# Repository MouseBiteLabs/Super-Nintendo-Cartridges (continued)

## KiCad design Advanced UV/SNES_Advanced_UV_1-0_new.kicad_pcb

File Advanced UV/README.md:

# Super Nintendo Advanced UV Cartridge (SNES-8XJ8D-01C)

This is an updated design of my old <a href="https://mousebitelabs.com/2020/07/08/multi-function-snes-reproduction-board-guide/">SNES Advanced cartridge boards</a>, which utilize older UV EPROM chips 27C160 and/or 27C322. Functionally, this design is the same as the older one, but under the hood I have ported the project over from Eagle to KiCad, and heavily cleaned up the schematic and some of the trace routings. This version is also fully open source.

This cartridge covers over 95% of the entire SNES library, capable of any standard cartridge **but not those with co-processors, such as SA-1 or SuperFX.** You can backup games onto it with the following settings:
- All memory maps supported: LoROM, HiROM, ExLoROM, and ExHiROM
- Can be programmed to operate as a multicart, changing games by pressing the SNES reset button
- Up to 8 MB of ROM space for a single game or 4 MB of ROM space for two games
- Up to 128 KB of RAM space for a single game or two separate banks of 64 KB RAM space for two games

All gerbers and source files can be found in this repo, as again, this project is fully open source. Please read all instructions before attempting the project.

## Tutorial Video

This video is older, but still applies to this board.

## Important Things Before You Start

1) <a href="https://github.com/MouseBiteLabs/Super-Nintendo-Cartridges/wiki">Please review the wiki for more information about using the circuit boards, instructions for how to program them, and example builds.</a>
2) When soldering parts on, it's a good idea to put kapton tape or otherwise cover the bottom cartridge edge. You do not want to get solder on the cartridge contacts.
3) I am not responsible for any damage you do to your self or your property. Attempt this project at your own risk.
4) I do not guarantee design compatibility. You may encounter issues with certain games. There is also a chance I have made an error in the design or the BOM - if this is the case, I will do everything I can to address the problem as quickly as possible.
5) If you are using this board to make games other than for personal use, you must have permission from the originator to use and distribute any ROM images or other related material. You are responsible for making sure you adhere to any license requirements.

DO NOT use my circuit boards for profiting from stolen work - this especially includes homebrew content, ROM hacks, and using fan-made labels without permission from the originator. **Support ALL original creators!**

## Board Characteristics and Order Information

The zipped folder contains all the gerber files for this board. The following options **must** be chosen when ordering boards for yourself.

- Thickness: 1.2mm
- Surface Finish: ENIG
- Gold Fingers: Yes, 30° chamfer

You can use the zipped folder at any board fabricator you like. You may also buy the board from PCBWay using this link (disclosure: I receive 10% of the sale value to go towards future PCB orders of my own):

### Purchase from My Website

You can purchase this circuit board at my website, [https://mousebitelabs.store](https://mousebitelabs.store). Click the following image to be directed to the specific item listing:

### Purchase from Etsy

I also offer the board on Etsy, if you would rather purchase through there - click the banner to be redirected.

## Required Equipment

- You will need basic tools, like a soldering iron.
- You need a way to program the ROM chip(s). There are two ways I have programmed them in the past:
  - Using the <a href="https://xgecu.myshopify.com/products/xgecu-new-t48-tl866-3gprogrammer-v12-01-support-28000-ics-for-spi-nor-nand-flash-emmc-bga153-162-169-100-221-tsop-sop-plcc">T48 programmer</a> with my <a href="https://github.com/MouseBiteLabs/27C322-TL866-Adapter">27C322 to TL866 Programming Adatper</a> board. The programming adapter is compatible with the T48, and it allows you to program the 42-pin EPROMs (27C160 and 27C322) with the 40-pin T48 programmer.
  OR
  - Using the <a href="https://www.mcumall.com/store/index.php?route=product/product&path=66&product_id=85">GQ4x4 programmer</a> with the ZIF adapter board that comes with it.
- This cartridge uses the PIC12F629 with the <a href="https://sd2snes.de/blog/cool-stuff/supercic">SuperCIC code</a> to fake out the lockout chip. You will need a way to program these PIC chips. I use the T48 to do so, but you can also use something like the <a href="https://www.microchip.com/en-us/development-tool/pg164130">PICkit 3.</a> Note that if you have region modded your SNES, you won't need the lockout chips in the cartridges.

## How to Program

<a href="https://github.com/MouseBiteLabs/Super-Nintendo-Cartridges/wiki/Preparing-the-ROM">Please check out the wiki pages on how to prepare the ROM and program the cartridge.</a>

## Board Configurations

This board is highly customizable. You *do not* need every single part on this board to make a game. The game you want to make is mainly dependent on the memory mapping (LoROM, HiROM, etc), the ROM size, and the RAM size. Depending on your needs, you only need to solder on certain components, which you can find below in the BOM section. You will also need to configure the game with the various solder jumpers on the back of the board.

<a href="https://github.com/MouseBiteLabs/Super-Nintendo-Cartridges/wiki/Advanced-UV">**I highly recommend checking out the various examples of board configurations on the wiki.**</a>

### Components Required

I've split up the requisite parts into a few different "Groups" which you can find a comprehensive list for in the BOM section a few sections down from this one.

- **Every board needs Group A components.** You can make LoRom or HiROM games that have no RAM and are up to 4 MB large with this configuration.
- If you need RAM space, **add Group B components.** This will add up to 128 KB of RAM space.
- If your game is larger than 4 MB, it will use the ExLoROM or ExHiROM memory mapping. **Add Group C components for this.**
- For multicarts, you can make a board with two games on it up to 4 MB each. You will need Group C components, **as well as Group D components.**

#### Socket Configurations

If your game is the LoROM or ExLoROM mapping type, solder U3 (and U4 if necessary) in the bottom set of sockets (labeled "LO" on the left side). If your game is of the HiROM or ExHiROM mapping type, solder U3 (and U4 if necessary) in the top set of sockets (labeled "HI" on the left side). Furthermore, if you are making a LoROM or ExLoROM game that has SRAM, then populate the U8L socket. If you are making a HiROM or ExHiROM game that has SRAM, then populate the U8H socket. Note that you can populate both U8L and U8H without issue, if you want.

If you are making a multicart, both games must be of the *same* mapping type. You cannot make one HiROM and one LoROM game in a multicart.

Keep in mind that the 27C160 can hold up to 2 MB of ROM data, and the 27C322 can hold up to 4 MB. You can use either of those chips in ROM slots 1 and 2, but if you are going to make an ExLoROM or ExHiROM game, ROM1 needs to be a 27C322. ROM2 in this case *can* be a 27C160, but only if the ROM is 6 MB total in size.

### Solder Jumpers

There are two types of solder jumper pads on the board - the 2-segment and 3-segment. For the 2-segment pads, if they need to be connected, simply bridge the two with solder. For the 3-segment pads, use a solder bridge on the middle pad to either side depending on the option you need.

#### U8 Bypass

This is the only set of pads on the front of the board. If your game does not use SRAM, then you must solder these pads together. **Do not solder these pads if your game uses SRAM.**

#### U3/U4 Configuration

On the reverse side of U3 and U4 are three sets of pads used to set what kind of EPROM you are using, and in the case of the 27C322, what mapping type you are using.

Keep in mind that if you are using both ROM1 and ROM2, both EPROMs *must* be in the same mapping type sockets - either both LoROM or both HiROM. You cannot mix the two mapping types between EPROMs. You can however use one 27C322 in ROM1 and a 27C160 in ROM2 for EX-mode games, or 27C160 in ROM1 as well if making a multicart.

#### LoROM/HiROM

These are all 3-segment pads. They only need to be configured on the back if you are making a game that contains SRAM.

#### Single/Multi

The pads on the bottom right of the back of the board are mandatory for every game. Solder the middle pad to the top for single game configuration, or to the bottom for multicart configuration. The pads on the top middle of the back of the board only need to be configured if your cartridge uses SRAM.

#### SRAM Size

The set of pads at the top left underneath the SRAM chip configure the size of the SRAM that the SNES will see. All pads must be configured if you are using SRAM, and each set of 2 should be soldered in the same direction. The example picture below shows a game configured for 256 Kbit of SRAM. **It is important to note these numbers represent the SRAM in BITS, not BYTES. To figure out the BYTES of SRAM, take the numbers here and divide by 8.**

Note: If you want to set the RAM size to zero, but still have a RAM chip installed, then simply unsolder the right-most HIROM/LOROM solder pads on the backside of the board.

### Multicart Configuration

If you are setting you cartridge up for a multicart, you must bend out pin 2 (AS6C1008) or pin 1 (AS6C62256) on the SRAM chip and solder it to the outside hole.

## Estimating Battery Life

To accurately estimate the battery life, measure the voltage across R1 using a multimeter in DC mV mode, touching the probes to the two test point pads on either side of R1. You should read something around 1 mV or less. If you are severely higher than 10 mV, like in the 100's of mV, then you have a problem on your board.

Once you have a suitable voltage, find the milliamp-hour rating of your selected battery (preferrably from a datasheet). For example, a Renata CR2032 battery is rated for 225 mAh.

Now to estimate battery life, take the voltage measurement in mV and the battery rating in mAh, and plug it into this equation: 

Time (years) = Resistance of R1 (ohms) * Battery capacity (mAh) / Voltage (mV) / 8760

The factor of 8760 is for converting years to hours (24 hours in a day, 365 days in a year). The resistance of R1 is 1000 ohms. So for an example, if you measured 1 mV on R1 and are using a Renata CR2032, you would get 1000 * 225 / 1 / 8760 = **25.7 years.**

## Troubleshooting

<a href="https://github.com/MouseBiteLabs/Super-Nintendo-Cartridges/wiki/Troubleshooting-Tips">Please check out the wiki pages for troubleshooting tips.</a>

## Bill of Materials (BOM)

The component groups required for the build you want to make are detailed above.

### Mouser Shopping Cart

The following cart has *the maximum amount* of parts you would potentially need on a single board (essentially, a multicart), plus a few extras of the passive components due to price breaks. Importantly, though, this does not include the UV EPROM chips (27C160 and 27C322) because those are only available as old stock from places like AliExpress and/or eBay.

https://www.mouser.com/ProjectManager/ProjectDetail.aspx?AccessID=686eaad9eb

### Group A - 4 MB ROM, No RAM

| Reference | Value/Part Number | Package              | Description                     | Source                                           |
| --------- | ----------------- | -------------------- | ------------------------------- | ------------------------------------------------ |
| C1        | 22u               | Radial 2.5mm spacing | Aluminum Electrolytic Capacitor | [https://mou.sr/4lzfiK1](https://mou.sr/4lzfiK1) |
| C2        | 0.1u              | Radial 2.5mm spacing | Ceramic Capacitor               | [https://mou.sr/481ILov](https://mou.sr/481ILov) |
| C3        | 0.1u              | Radial 2.5mm spacing | Ceramic Capacitor               | [https://mou.sr/481ILov](https://mou.sr/481ILov) |
| C6        | 0.1u              | Radial 2.5mm spacing | Ceramic Capacitor               | [https://mou.sr/481ILov](https://mou.sr/481ILov) |
| C7        | 0.1u              | Radial 2.5mm spacing | Ceramic Capacitor               | [https://mou.sr/481ILov](https://mou.sr/481ILov) |
| C9        | 0.1u              | Radial 2.5mm spacing | Ceramic Capacitor               | [https://mou.sr/481ILov](https://mou.sr/481ILov) |
| U2A       | PIC12F629         | DIP-8                | PIC Microcontroller             | [https://mou.sr/3XuEZzO](https://mou.sr/3XuEZzO) |
| U2B       | PIC12F629         | SOIC-8               | PIC Microcontroller             | [https://mou.sr/4dSUh90](https://mou.sr/4dSUh90) |
| U3        | 27C322, 27C160    | DIP-42               | UV EPROM                        | AliExpress, eBay                                 |
| U6        | 74HCT257          | DIP-16               | Multiplexer                     | [https://mou.sr/3EvChVI](https://mou.sr/3EvChVI) |
| U7        | 74HCT257          | DIP-16               | Multiplexer                     | [https://mou.sr/3EvChVI](https://mou.sr/3EvChVI) |
| U9        | 74HCT139          | DIP-16               | Decoder                         | [https://mou.sr/441VXuJ](https://mou.sr/441VXuJ) |

### Group B - adds 32 KB of RAM

| Reference | Value/Part Number | Package              | Description                     | Source                                           |
| --------- | ----------------- | -------------------- | ------------------------------- | ------------------------------------------------ |
| B1        | CR2032            | CR2032               | Coin Cell Battery               | [https://mou.sr/3Wj2m0G](https://mou.sr/3Wj2m0G) |
| CB        | 22u               | Radial 2.5mm spacing | Aluminum Electrolytic Capacitor | [https://mou.sr/4lzfiK1](https://mou.sr/4lzfiK1) |
| C5        | 0.1u              | Radial 2.5mm spacing | Ceramic Capacitor               | [https://mou.sr/481ILov](https://mou.sr/481ILov) |
| C8        | 0.1u              | Radial 2.5mm spacing | Ceramic Capacitor               | [https://mou.sr/481ILov](https://mou.sr/481ILov) |
| D1        | BAT85             | DO-35-2              | Schottky Diode                  | [https://mou.sr/49GVT4m](https://mou.sr/49GVT4m) |
| D2        | BAT85             | DO-35-2              | Schottky Diode                  | [https://mou.sr/49GVT4m](https://mou.sr/49GVT4m) |
| D3        | BAT85             | DO-35-2              | Schottky Diode                  | [https://mou.sr/49GVT4m](https://mou.sr/49GVT4m) |
| Q1        | 2N3904            | TO-92-3 / SOT-23-3   | NPN BJT                         | THT: [https://mou.sr/3HlkU91](https://mou.sr/3HlkU91), SMT: [https://mou.sr/3C8piaZ](https://mou.sr/3C8piaZ) |
| R1        | 1k                | Axial                | Resistor                        | [https://mou.sr/4hYkrZr](https://mou.sr/4hYkrZr) |
| R2        | 100k              | Axial                | Resistor                        | [https://mou.sr/3Ib4SgO](https://mou.sr/3Ib4SgO) |
| R3        | 10k               | Axial                | Resistor                        | [https://mou.sr/42AN0WU](https://mou.sr/42AN0WU) |
| R4        | 1k                | Axial                | Resistor                        | [https://mou.sr/4hYkrZr](https://mou.sr/4hYkrZr) |
| R5        | 10k               | Axial                | Resistor                        | [https://mou.sr/42AN0WU](https://mou.sr/42AN0WU) |
| U5        | AS6C62256         | DIP-28               | SRAM                            | [https://mou.sr/3HlZ0mh](https://mou.sr/3HlZ0mh) |
| U8        | 74HCT139          | DIP-16               | Decoder                         | [https://mou.sr/441VXuJ](https://mou.sr/441VXuJ) |

### Group B (Optional) - adds 128 KB of RAM (instead of 32 KB)

Replace U5 in Group B above with the part detailed here, and add the other three components. **I personally recommend sticking to the AS6C62256 SRAM chip unless you absolutely need more RAM space.**

| Reference | Value/Part Number | Package | Description | Source                                           |
| --------- | ----------------- | ------- | ----------- | ------------------------------------------------ |
| Q2        | 2N3904            | TO-92-3 | NPN BJT     | [https://mou.sr/3HlkU91](https://mou.sr/3HlkU91) |
| R6        | 100k              | Axial   | Resistor    | [https://mou.sr/3Ib4SgO](https://mou.sr/3Ib4SgO) |
| R7        | 10k               | Axial   | Resistor    | [https://mou.sr/42AN0WU](https://mou.sr/42AN0WU) |
| U5        | AS6C1008          | DIP-32  | SRAM        | [https://mou.sr/3hNkGxg](https://mou.sr/3hNkGxg) |

### Group C - Adds 4 MB ROM for ExLoROM/ExHiROM or multicarts

| Reference | Value/Part Number | Package              | Description       | Source                                           |
| --------- | ----------------- | -------------------- | ----------------- | ------------------------------------------------ |
| C4        | 0.1u              | Radial 2.5mm spacing | Ceramic Capacitor | [https://mou.sr/481ILov](https://mou.sr/481ILov) |
| U4        | 27C322, 27C160    | DIP-42               | UV EPROM          | AliExpress, eBay                                 |

### Group D - Enables multicart mode

| Reference | Value/Part Number | Package              | Description       | Source                                           |
| --------- | ----------------- | -------------------- | ----------------- | ------------------------------------------------ |
| C10       | 0.1u              | Radial 2.5mm spacing | Ceramic Capacitor | [https://mou.sr/481ILov](https://mou.sr/481ILov) |
| U10       | 74HCT74           | DIP-14               | Flip-flop         | [https://mou.sr/3YEiVo8](https://mou.sr/3YEiVo8) |

## Revision History

### v1.0 - Re-release

- Release of the KiCad-ported version of my original SNES Advanced cart design
- Removed the "SRAM Enable" pads and made the SRAM always enabled
- HOTFIX: changed QR code, added open source hardware logo

## Acknowledgements

- Continual thanks to all in the nesdev community for their resources, design tips, and support throughout the past half-decade. This design was one of my original ones that was improved through their help and feedback when I was first starting out.

## License

<br />This work is licensed under a <a rel="license" href="http://creativecommons.org/licenses/by-sa/4.0/">Creative Commons Attribution-ShareAlike 4.0 International License</a>. You are able to copy and redistribute the material in any medium or format, as well as remix, transform, or build upon the material for any purpose (even commercial) - but you **must** give appropriate credit, provide a link to the license, and indicate if any changes were made.

©MouseBiteLabs 2025

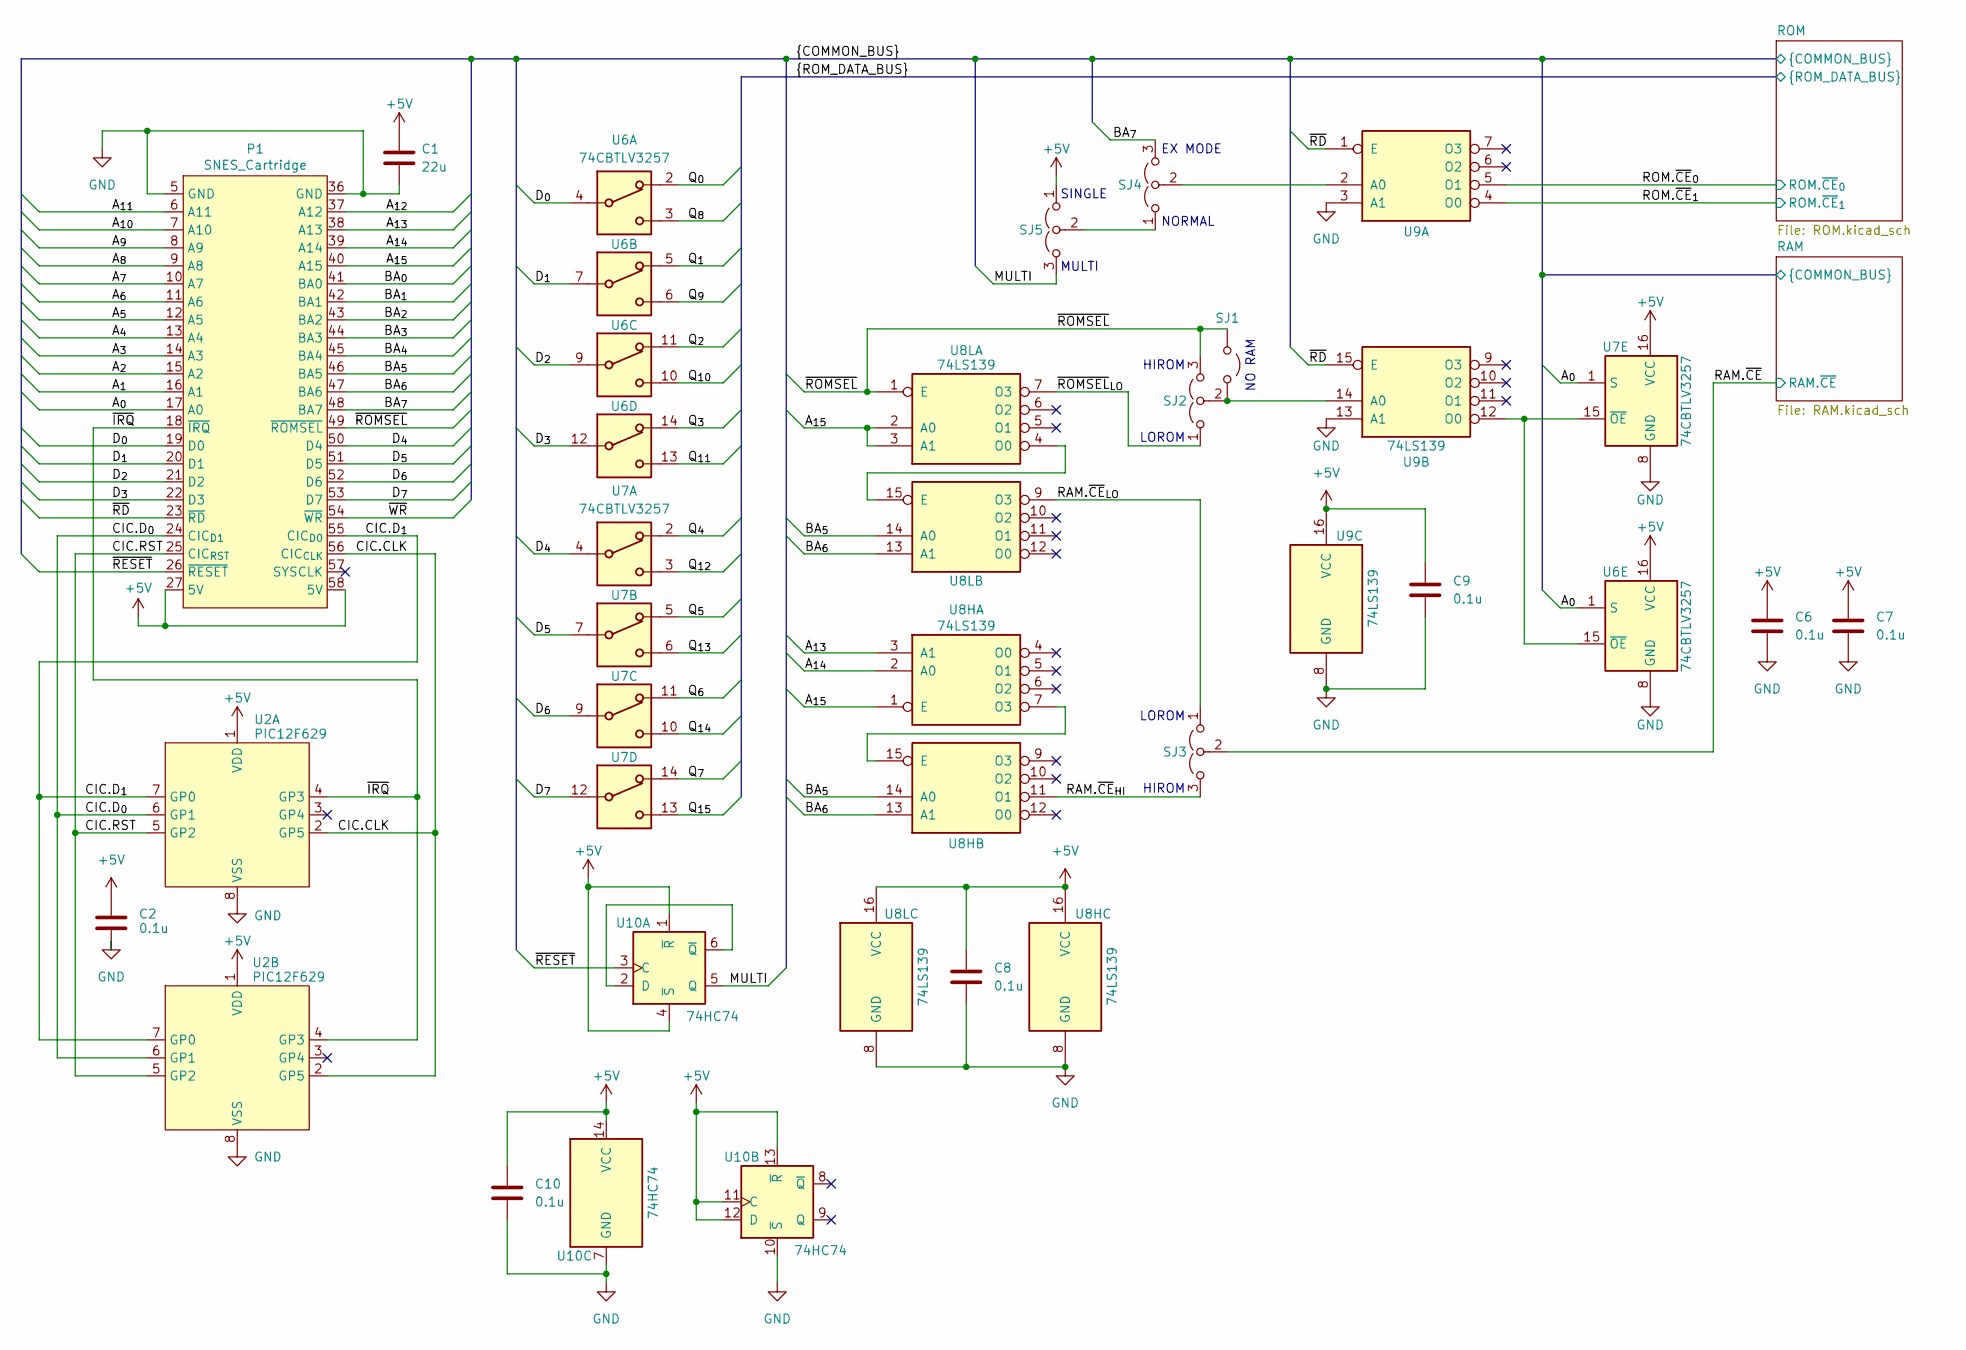
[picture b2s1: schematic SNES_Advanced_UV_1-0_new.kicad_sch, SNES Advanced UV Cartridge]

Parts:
C1: 22u; CP_Radial_D5.0mm_P2.50mm
C2, C6, C7, C8, C9, C10: 0.1u; C_THT
P1: SNES_Cartridge; Cart_Edge_SNES_Standard
SJ1: Jumper_2_Open; SJ
SJ2, SJ3, SJ4, SJ5: Jumper_3_Open; SJ_2
U2A: PIC12F629; SOIC-8_3.9x4.9mm_P1.27mm
U2B: PIC12F629; DIP-8_W7.62mm
U6, U7: 74CBTLV3257; DIP-16_W7.62mm
U8H, U8L, U9: 74LS139; DIP-16_W7.62mm
U10: 74HC74; DIP-14_W7.62mm

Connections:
+5V: C1.1, C2.1, C6.1, C7.1, C8.1, C9.1, C10.1, P1.27 (5V), P1.58 (5V), SJ5.1 (A), U2A.1 (VDD), U2B.1 (VDD), U6.16 (VCC), U7.16 (VCC), U8H.16 (VCC), U8L.16 (VCC), U9.16 (VCC), U10.1 (~R), U10.4 (~S), U10.11 (C), U10.12 (D), U10.13 (~R), U10.14 (VCC); also elsewhere on the board
/A_{0}: P1.17 (A0), U6.1 (S), U7.1 (S); also elsewhere on the board
/A_{1}: P1.16 (A1); also elsewhere on the board
/A_{2}: P1.15 (A2); also elsewhere on the board
/A_{3}: P1.14 (A3); also elsewhere on the board
/A_{4}: P1.13 (A4); also elsewhere on the board
/A_{5}: P1.12 (A5); also elsewhere on the board
/A_{6}: P1.11 (A6); also elsewhere on the board
/A_{7}: P1.10 (A7); also elsewhere on the board
/A_{8}: P1.9 (A8); also elsewhere on the board
/A_{9}: P1.8 (A9); also elsewhere on the board
/A_{10}: P1.7 (A10); also elsewhere on the board
/A_{11}: P1.6 (A11); also elsewhere on the board
/A_{12}: P1.37 (A12); also elsewhere on the board
/A_{13}: P1.38 (A13), U8H.3 (A1); also elsewhere on the board
/A_{14}: P1.39 (A14), U8H.2 (A0); also elsewhere on the board
/A_{15}: P1.40 (A15), U8H.1 (E), U8L.2 (A0), U8L.3 (A1); also elsewhere on the board
/BA_{0}: P1.41 (BA0); also elsewhere on the board
/BA_{1}: P1.42 (BA1); also elsewhere on the board
/BA_{2}: P1.43 (BA2); also elsewhere on the board
/BA_{3}: P1.44 (BA3); also elsewhere on the board
/BA_{4}: P1.45 (BA4); also elsewhere on the board
/BA_{5}: P1.46 (BA5), U8H.14 (A0), U8L.14 (A0); also elsewhere on the board
/BA_{6}: P1.47 (BA6), U8H.13 (A1), U8L.13 (A1); also elsewhere on the board
/BA_{7}: P1.48 (BA7), SJ4.3 (B)
/CIC.CLK: P1.56 (CIC_{CLK}), U2A.2 (GP5), U2B.2 (GP5)
/CIC.D_{0}: P1.55 (CIC_{D0}), U2A.7 (GP0), U2B.7 (GP0)
/CIC.D_{1}: P1.24 (CIC_{D1}), U2A.6 (GP1), U2B.6 (GP1)
/CIC.RST: P1.25 (CIC_{RST}), U2A.5 (GP2), U2B.5 (GP2)
/D_{0}: P1.19 (D0), U6.4; also elsewhere on the board
/D_{1}: P1.20 (D1), U6.7; also elsewhere on the board
/D_{2}: P1.21 (D2), U6.9; also elsewhere on the board
/D_{3}: P1.22 (D3), U6.12; also elsewhere on the board
/D_{4}: P1.50 (D4), U7.4; also elsewhere on the board
/D_{5}: P1.51 (D5), U7.7; also elsewhere on the board
/D_{6}: P1.52 (D6), U7.9; also elsewhere on the board
/D_{7}: P1.53 (D7), U7.12; also elsewhere on the board
/MULTI: SJ5.3 (B), U10.5 (Q); also elsewhere on the board
/Q_{0}: U6.2; also elsewhere on the board
/Q_{1}: U6.5; also elsewhere on the board
/Q_{2}: U6.11; also elsewhere on the board
/Q_{3}: U6.14; also elsewhere on the board
/Q_{4}: U7.2; also elsewhere on the board
/Q_{5}: U7.5; also elsewhere on the board
/Q_{6}: U7.11; also elsewhere on the board
/Q_{7}: U7.14; also elsewhere on the board
/Q_{8}: U6.3; also elsewhere on the board
/Q_{9}: U6.6; also elsewhere on the board
/Q_{10}: U6.10; also elsewhere on the board
/Q_{11}: U6.13; also elsewhere on the board
/Q_{12}: U7.3; also elsewhere on the board
/Q_{13}: U7.6; also elsewhere on the board
/Q_{14}: U7.10; also elsewhere on the board
/Q_{15}: U7.13; also elsewhere on the board
/RAM.~CE: SJ3.2 (C); also elsewhere on the board
/RAM.~CE_{HI}: SJ3.3 (B), U8H.11 (O1)
/RAM.~CE_{LO}: SJ3.1 (A), U8L.9 (O3)
/ROM.~CE_{0}: U9.5 (O1); also elsewhere on the board
/ROM.~CE_{1}: U9.4 (O0); also elsewhere on the board
/~IRQ: P1.18 (~IRQ), U2A.4 (GP3), U2B.4 (GP3)
/~RD: P1.23 (~RD), U9.1 (E), U9.15 (E); also elsewhere on the board
/~RESET: P1.26 (~RESET), U10.3 (C); also elsewhere on the board
/~ROMSEL: P1.49 (~ROMSEL), SJ1.2 (B), SJ2.3 (B), U8L.1 (E)
/~ROMSEL_{LO}: SJ2.1 (A), U8L.7 (O3)
/~WR: P1.54 (~WR); also elsewhere on the board
GND: C1.2, C2.2, C6.2, C7.2, C8.2, C9.2, C10.2, P1.5 (GND), P1.36 (GND), U2A.8 (VSS), U2B.8 (VSS), U6.8 (GND), U7.8 (GND), U8H.8 (GND), U8L.8 (GND), U9.3 (A1), U9.8 (GND), U9.13 (A1), U10.7 (GND), U10.10 (~S); also elsewhere on the board
unnamed: SJ1.1 (A), SJ2.2 (C), U9.14 (A0)
unnamed: SJ4.1 (A), SJ5.2 (C)
unnamed: SJ4.2 (C), U9.2 (A0)
unnamed: U6.15 (~OE), U7.15 (~OE), U9.12 (O0)
unnamed: U8H.7 (O3), U8H.15 (E)
unnamed: U8L.4 (O0), U8L.15 (E)
unnamed: U10.2 (D), U10.6 (~Q)

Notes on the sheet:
SINGLE MULTI
HIROM LOROM
NO RAM
EX MODE NORMAL
LOROM HIROM

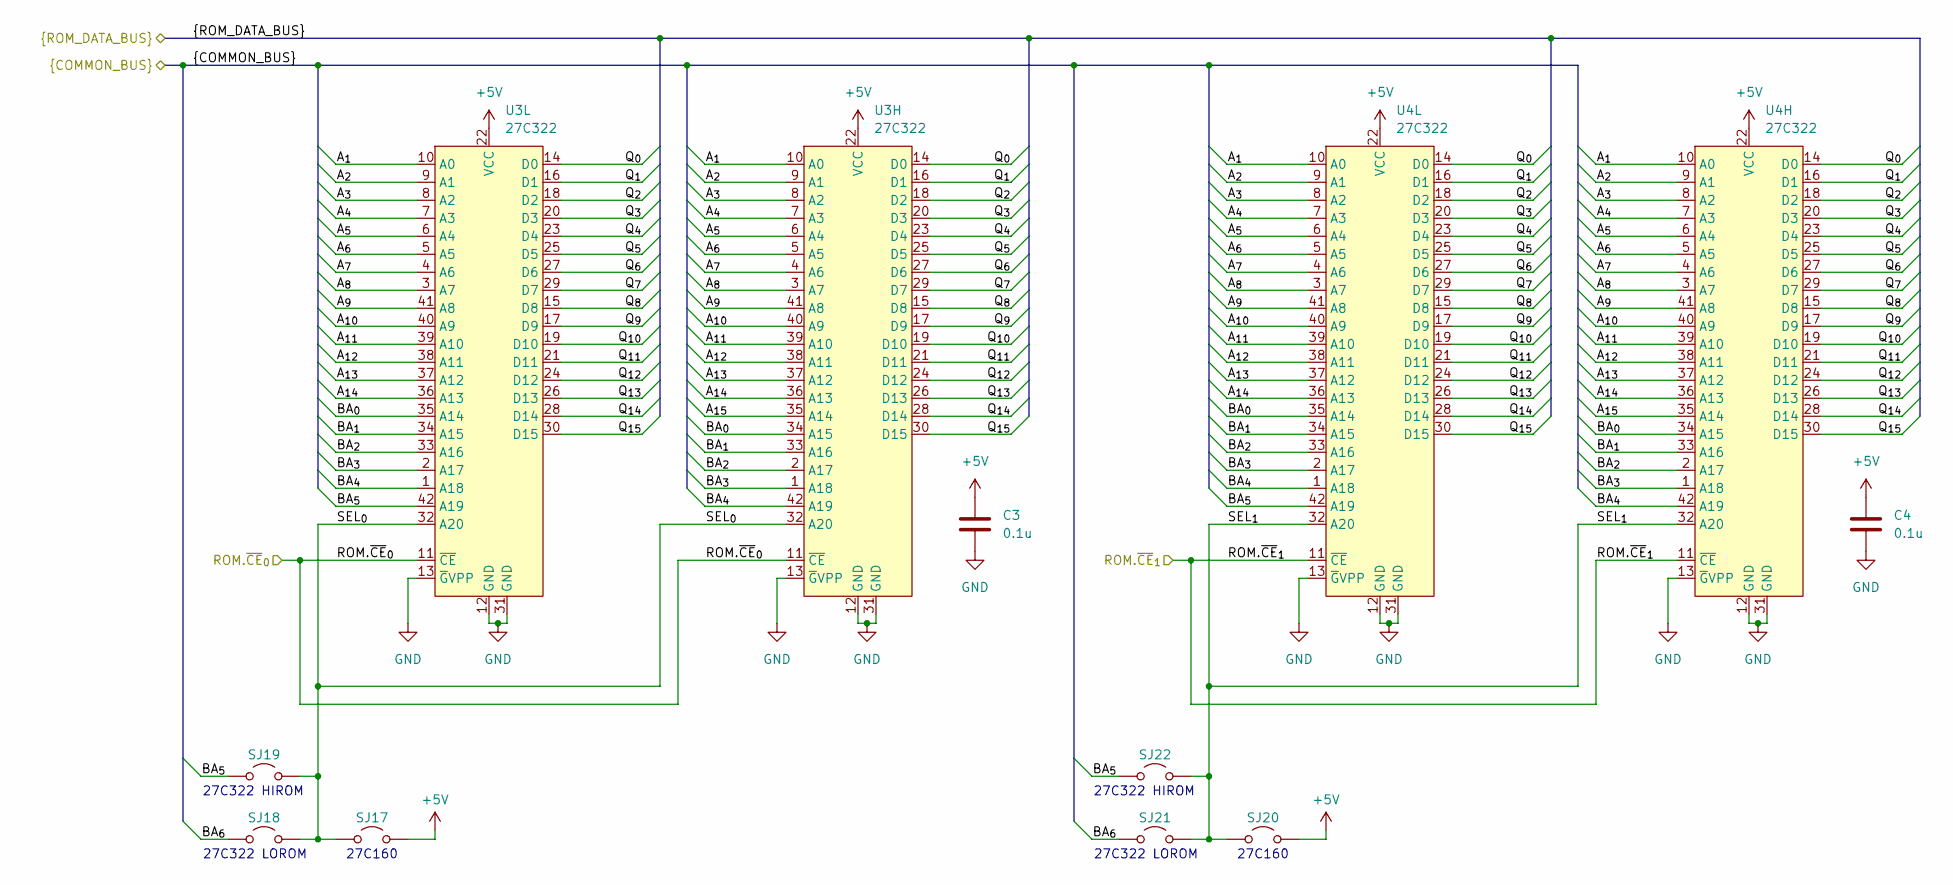
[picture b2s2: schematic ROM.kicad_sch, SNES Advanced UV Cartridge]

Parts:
C3, C4: 0.1u; C_THT
SJ17, SJ18, SJ19, SJ20, SJ21, SJ22: Jumper_2_Open; SJ
U3H, U3L, U4H, U4L: 27C322; DIP-42_W15.24mm

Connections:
+5V: C3.1, C4.1, SJ17.1 (A), SJ20.1 (A), U3H.22 (VCC), U3L.22 (VCC), U4H.22 (VCC), U4L.22 (VCC); also elsewhere on the board
/A_{1}: U3H.10 (A0), U3L.10 (A0), U4H.10 (A0), U4L.10 (A0); also elsewhere on the board
/A_{2}: U3H.9 (A1), U3L.9 (A1), U4H.9 (A1), U4L.9 (A1); also elsewhere on the board
/A_{3}: U3H.8 (A2), U3L.8 (A2), U4H.8 (A2), U4L.8 (A2); also elsewhere on the board
/A_{4}: U3H.7 (A3), U3L.7 (A3), U4H.7 (A3), U4L.7 (A3); also elsewhere on the board
/A_{5}: U3H.6 (A4), U3L.6 (A4), U4H.6 (A4), U4L.6 (A4); also elsewhere on the board
/A_{6}: U3H.5 (A5), U3L.5 (A5), U4H.5 (A5), U4L.5 (A5); also elsewhere on the board
/A_{7}: U3H.4 (A6), U3L.4 (A6), U4H.4 (A6), U4L.4 (A6); also elsewhere on the board
/A_{8}: U3H.3 (A7), U3L.3 (A7), U4H.3 (A7), U4L.3 (A7); also elsewhere on the board
/A_{9}: U3H.41 (A8), U3L.41 (A8), U4H.41 (A8), U4L.41 (A8); also elsewhere on the board
/A_{10}: U3H.40 (A9), U3L.40 (A9), U4H.40 (A9), U4L.40 (A9); also elsewhere on the board
/A_{11}: U3H.39 (A10), U3L.39 (A10), U4H.39 (A10), U4L.39 (A10); also elsewhere on the board
/A_{12}: U3H.38 (A11), U3L.38 (A11), U4H.38 (A11), U4L.38 (A11); also elsewhere on the board
/A_{13}: U3H.37 (A12), U3L.37 (A12), U4H.37 (A12), U4L.37 (A12); also elsewhere on the board
/A_{14}: U3H.36 (A13), U3L.36 (A13), U4H.36 (A13), U4L.36 (A13); also elsewhere on the board
/A_{15}: U3H.35 (A14), U4H.35 (A14); also elsewhere on the board
/BA_{0}: U3H.34 (A15), U3L.35 (A14), U4H.34 (A15), U4L.35 (A14); also elsewhere on the board
/BA_{1}: U3H.33 (A16), U3L.34 (A15), U4H.33 (A16), U4L.34 (A15); also elsewhere on the board
/BA_{2}: U3H.2 (A17), U3L.33 (A16), U4H.2 (A17), U4L.33 (A16); also elsewhere on the board
/BA_{3}: U3H.1 (A18), U3L.2 (A17), U4H.1 (A18), U4L.2 (A17); also elsewhere on the board
/BA_{4}: U3H.42 (A19), U3L.1 (A18), U4H.42 (A19), U4L.1 (A18); also elsewhere on the board
/BA_{5}: SJ19.2 (B), SJ22.2 (B), U3L.42 (A19), U4L.42 (A19); also elsewhere on the board
/BA_{6}: SJ18.1 (A), SJ21.1 (A); also elsewhere on the board
/Q_{0}: U3H.14 (D0), U3L.14 (D0), U4H.14 (D0), U4L.14 (D0); also elsewhere on the board
/Q_{1}: U3H.16 (D1), U3L.16 (D1), U4H.16 (D1), U4L.16 (D1); also elsewhere on the board
/Q_{2}: U3H.18 (D2), U3L.18 (D2), U4H.18 (D2), U4L.18 (D2); also elsewhere on the board
/Q_{3}: U3H.20 (D3), U3L.20 (D3), U4H.20 (D3), U4L.20 (D3); also elsewhere on the board
/Q_{4}: U3H.23 (D4), U3L.23 (D4), U4H.23 (D4), U4L.23 (D4); also elsewhere on the board
/Q_{5}: U3H.25 (D5), U3L.25 (D5), U4H.25 (D5), U4L.25 (D5); also elsewhere on the board
/Q_{6}: U3H.27 (D6), U3L.27 (D6), U4H.27 (D6), U4L.27 (D6); also elsewhere on the board
/Q_{7}: U3H.29 (D7), U3L.29 (D7), U4H.29 (D7), U4L.29 (D7); also elsewhere on the board
/Q_{8}: U3H.15 (D8), U3L.15 (D8), U4H.15 (D8), U4L.15 (D8); also elsewhere on the board
/Q_{9}: U3H.17 (D9), U3L.17 (D9), U4H.17 (D9), U4L.17 (D9); also elsewhere on the board
/Q_{10}: U3H.19 (D10), U3L.19 (D10), U4H.19 (D10), U4L.19 (D10); also elsewhere on the board
/Q_{11}: U3H.21 (D11), U3L.21 (D11), U4H.21 (D11), U4L.21 (D11); also elsewhere on the board
/Q_{12}: U3H.24 (D12), U3L.24 (D12), U4H.24 (D12), U4L.24 (D12); also elsewhere on the board
/Q_{13}: U3H.26 (D13), U3L.26 (D13), U4H.26 (D13), U4L.26 (D13); also elsewhere on the board
/Q_{14}: U3H.28 (D14), U3L.28 (D14), U4H.28 (D14), U4L.28 (D14); also elsewhere on the board
/Q_{15}: U3H.30 (D15), U3L.30 (D15), U4H.30 (D15), U4L.30 (D15); also elsewhere on the board
/ROM.~CE_{0}: U3H.11 (~CE), U3L.11 (~CE); also elsewhere on the board
/ROM.~CE_{1}: U4H.11 (~CE), U4L.11 (~CE); also elsewhere on the board
/ROM/SEL_{0}: SJ17.2 (B), SJ18.2 (B), SJ19.1 (A), U3H.32 (A20), U3L.32 (A20)
/ROM/SEL_{1}: SJ20.2 (B), SJ21.2 (B), SJ22.1 (A), U4H.32 (A20), U4L.32 (A20)
GND: C3.2, C4.2, U3H.12 (GND), U3H.13 (~GVPP), U3H.31 (GND), U3L.12 (GND), U3L.13 (~GVPP), U3L.31 (GND), U4H.12 (GND), U4H.13 (~GVPP), U4H.31 (GND), U4L.12 (GND), U4L.13 (~GVPP), U4L.31 (GND); also elsewhere on the board

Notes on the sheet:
27C160
27C322 LOROM
27C322 HIROM

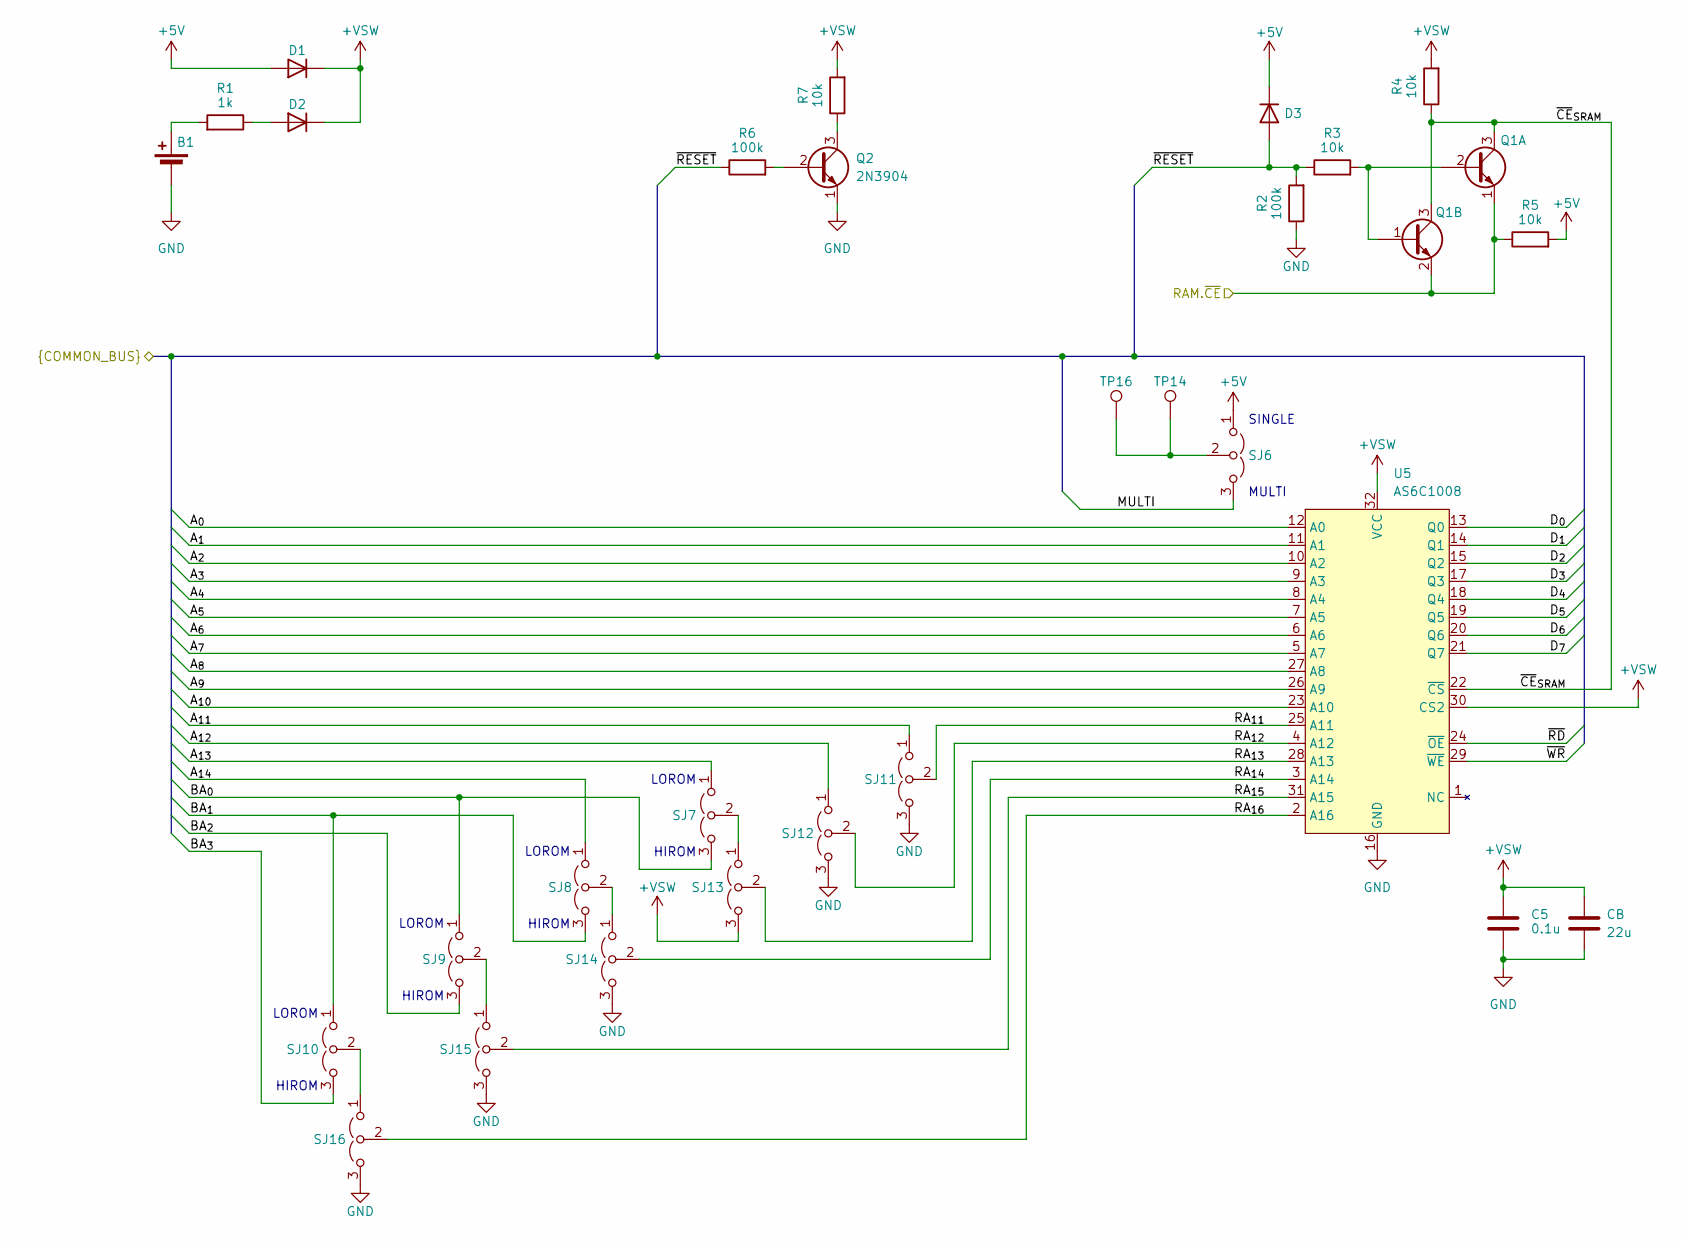
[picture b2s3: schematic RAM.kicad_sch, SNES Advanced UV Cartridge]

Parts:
B1: CR2025; COIN_CELL
C5: 0.1u; C_THT
CB: 22u; CP_Radial_D5.0mm_P2.50mm
D1, D2, D3: D; DIODE_THT_SMT
Q1A, Q2: 2N3904; TO-92L_Inline_Wide
Q1B: MMBT3904; SOT-23
R1: 1k; THT_SMT_0803
R2, R6: 100k; THT_SMT_0803
R3, R4, R5, R7: 10k; THT_SMT_0803
SJ6, SJ7, SJ8, SJ9, SJ10, SJ11, SJ12, SJ13, SJ14, SJ15, SJ16: Jumper_3_Open; SJ_2
TP14, TP16: TPB1,27; TestPoint_THTPad_D1.5mm_Drill0.7mm
U5: AS6C1008; DIP-32_W15.24mm

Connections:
+5V: D1.2 (A), D3.1 (K), R5.2, SJ6.1 (A); also elsewhere on the board
+VSW: C5.1, CB.1, D1.1 (K), D2.1 (K), R4.2, R7.2, SJ13.3 (B), U5.30 (CS2), U5.32 (VCC)
/A_{0}: U5.12 (A0); also elsewhere on the board
/A_{1}: U5.11 (A1); also elsewhere on the board
/A_{2}: U5.10 (A2); also elsewhere on the board
/A_{3}: U5.9 (A3); also elsewhere on the board
/A_{4}: U5.8 (A4); also elsewhere on the board
/A_{5}: U5.7 (A5); also elsewhere on the board
/A_{6}: U5.6 (A6); also elsewhere on the board
/A_{7}: U5.5 (A7); also elsewhere on the board
/A_{8}: U5.27 (A8); also elsewhere on the board
/A_{9}: U5.26 (A9); also elsewhere on the board
/A_{10}: U5.23 (A10); also elsewhere on the board
/A_{11}: SJ11.1 (A); also elsewhere on the board
/A_{12}: SJ12.1 (A); also elsewhere on the board
/A_{13}: SJ7.1 (A); also elsewhere on the board
/A_{14}: SJ8.1 (A); also elsewhere on the board
/BA_{0}: SJ7.3 (B), SJ9.1 (A); also elsewhere on the board
/BA_{1}: SJ8.3 (B), SJ10.1 (A); also elsewhere on the board
/BA_{2}: SJ9.3 (B); also elsewhere on the board
/BA_{3}: SJ10.3 (B); also elsewhere on the board
/D_{0}: U5.13 (Q0); also elsewhere on the board
/D_{1}: U5.14 (Q1); also elsewhere on the board
/D_{2}: U5.15 (Q2); also elsewhere on the board
/D_{3}: U5.17 (Q3); also elsewhere on the board
/D_{4}: U5.18 (Q4); also elsewhere on the board
/D_{5}: U5.19 (Q5); also elsewhere on the board
/D_{6}: U5.20 (Q6); also elsewhere on the board
/D_{7}: U5.21 (Q7); also elsewhere on the board
/MULTI: SJ6.3 (B); also elsewhere on the board
/RAM.~CE: Q1A.1 (E), Q1B.2 (E), R5.1; also elsewhere on the board
/RAM/RA_{11}: SJ11.2 (C), U5.25 (A11)
/RAM/RA_{12}: SJ12.2 (C), U5.4 (A12)
/RAM/RA_{13}: SJ13.2 (C), U5.28 (A13)
/RAM/RA_{14}: SJ14.2 (C), U5.3 (A14)
/RAM/RA_{15}: SJ15.2 (C), U5.31 (A15)
/RAM/RA_{16}: SJ16.2 (C), U5.2 (A16)
/RAM/~CE_{SRAM}: Q1A.3 (C), Q1B.3 (C), R4.1, U5.22 (~CS)
/~RD: U5.24 (~OE); also elsewhere on the board
/~RESET: D3.2 (A), R2.2, R3.1, R6.1; also elsewhere on the board
/~WR: U5.29 (~WE); also elsewhere on the board
GND: B1.2 (-), C5.2, CB.2, Q2.1 (E), R2.1, SJ11.3 (B), SJ12.3 (B), SJ14.3 (B), SJ15.3 (B), SJ16.3 (B), U5.16 (GND); also elsewhere on the board
unnamed: B1.1 (+), R1.2
unnamed: D2.2 (A), R1.1
unnamed: Q1A.2 (B), Q1B.1 (B), R3.2
unnamed: Q2.2 (B), R6.2
unnamed: Q2.3 (C), R7.1
unnamed: SJ6.2 (C), TP14.1, TP16.1
unnamed: SJ10.2 (C), SJ16.1 (A)
unnamed: SJ7.2 (C), SJ13.1 (A)
unnamed: SJ8.2 (C), SJ14.1 (A)
unnamed: SJ9.2 (C), SJ15.1 (A)

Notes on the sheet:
SINGLE MULTI
LOROM HIROM

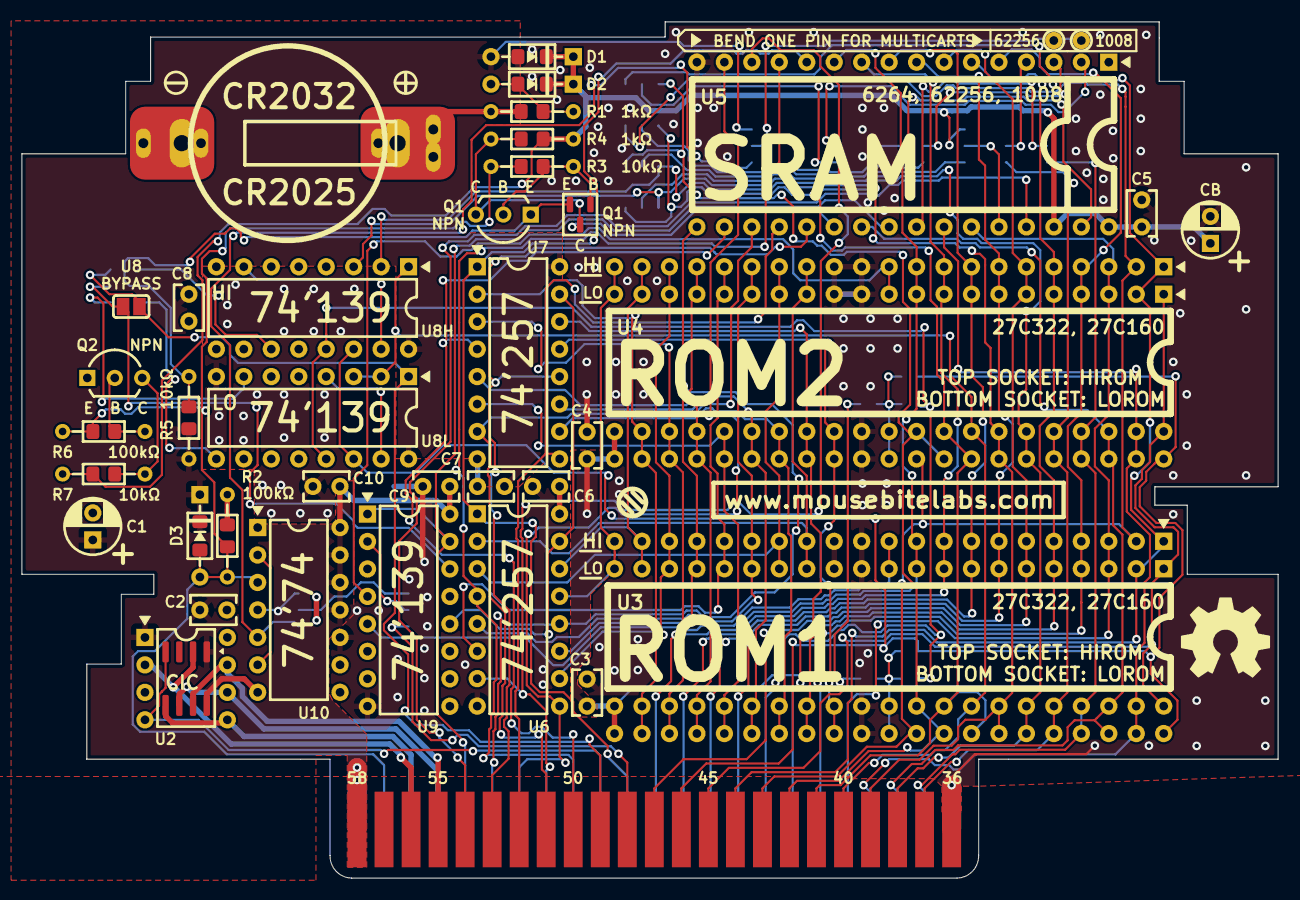
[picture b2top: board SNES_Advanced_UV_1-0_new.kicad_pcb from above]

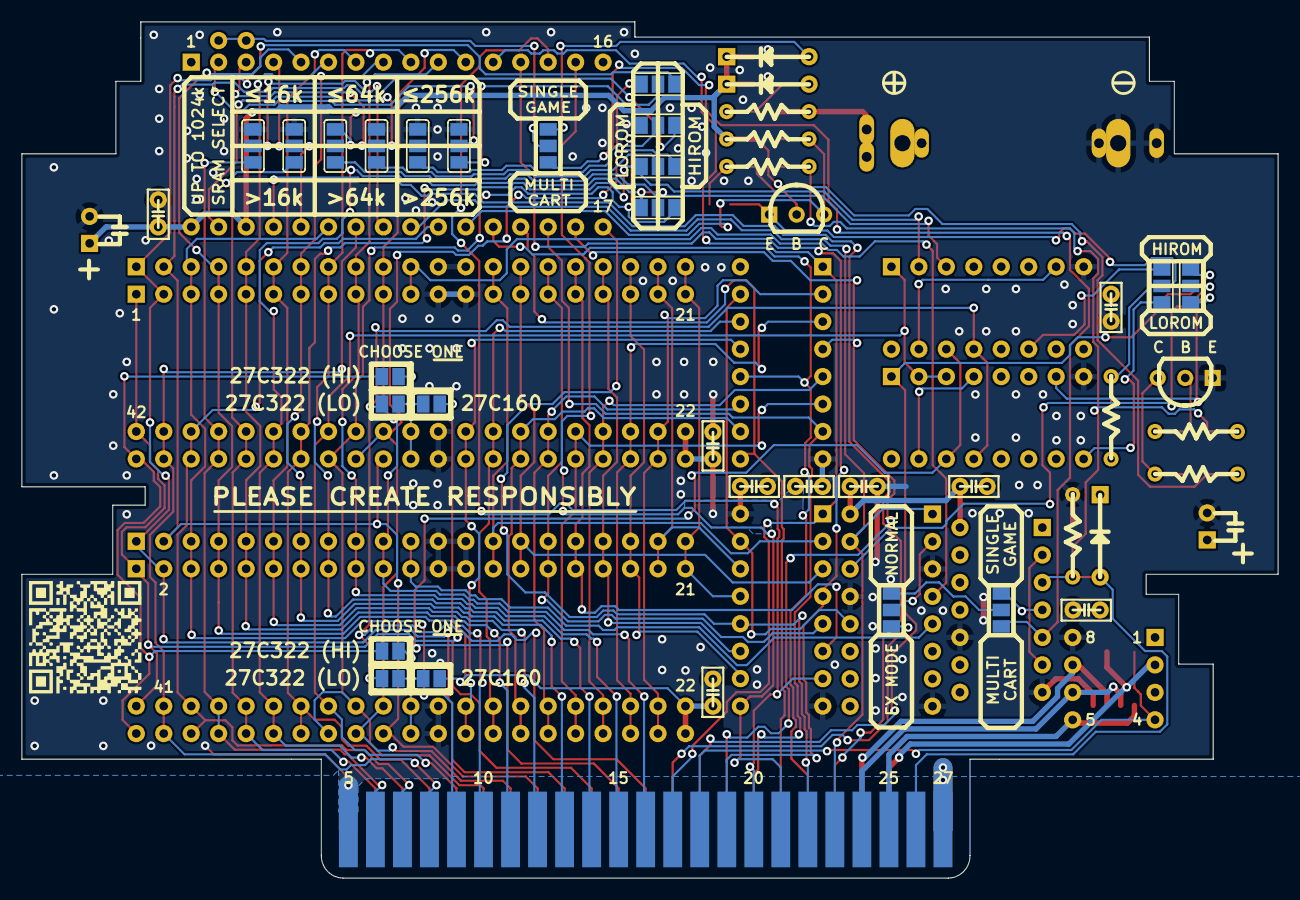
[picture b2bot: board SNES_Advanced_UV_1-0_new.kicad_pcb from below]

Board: 2 copper layers, 116.2 x 79.2 mm, 63 parts (21 on the bottom side), 93 nets.
